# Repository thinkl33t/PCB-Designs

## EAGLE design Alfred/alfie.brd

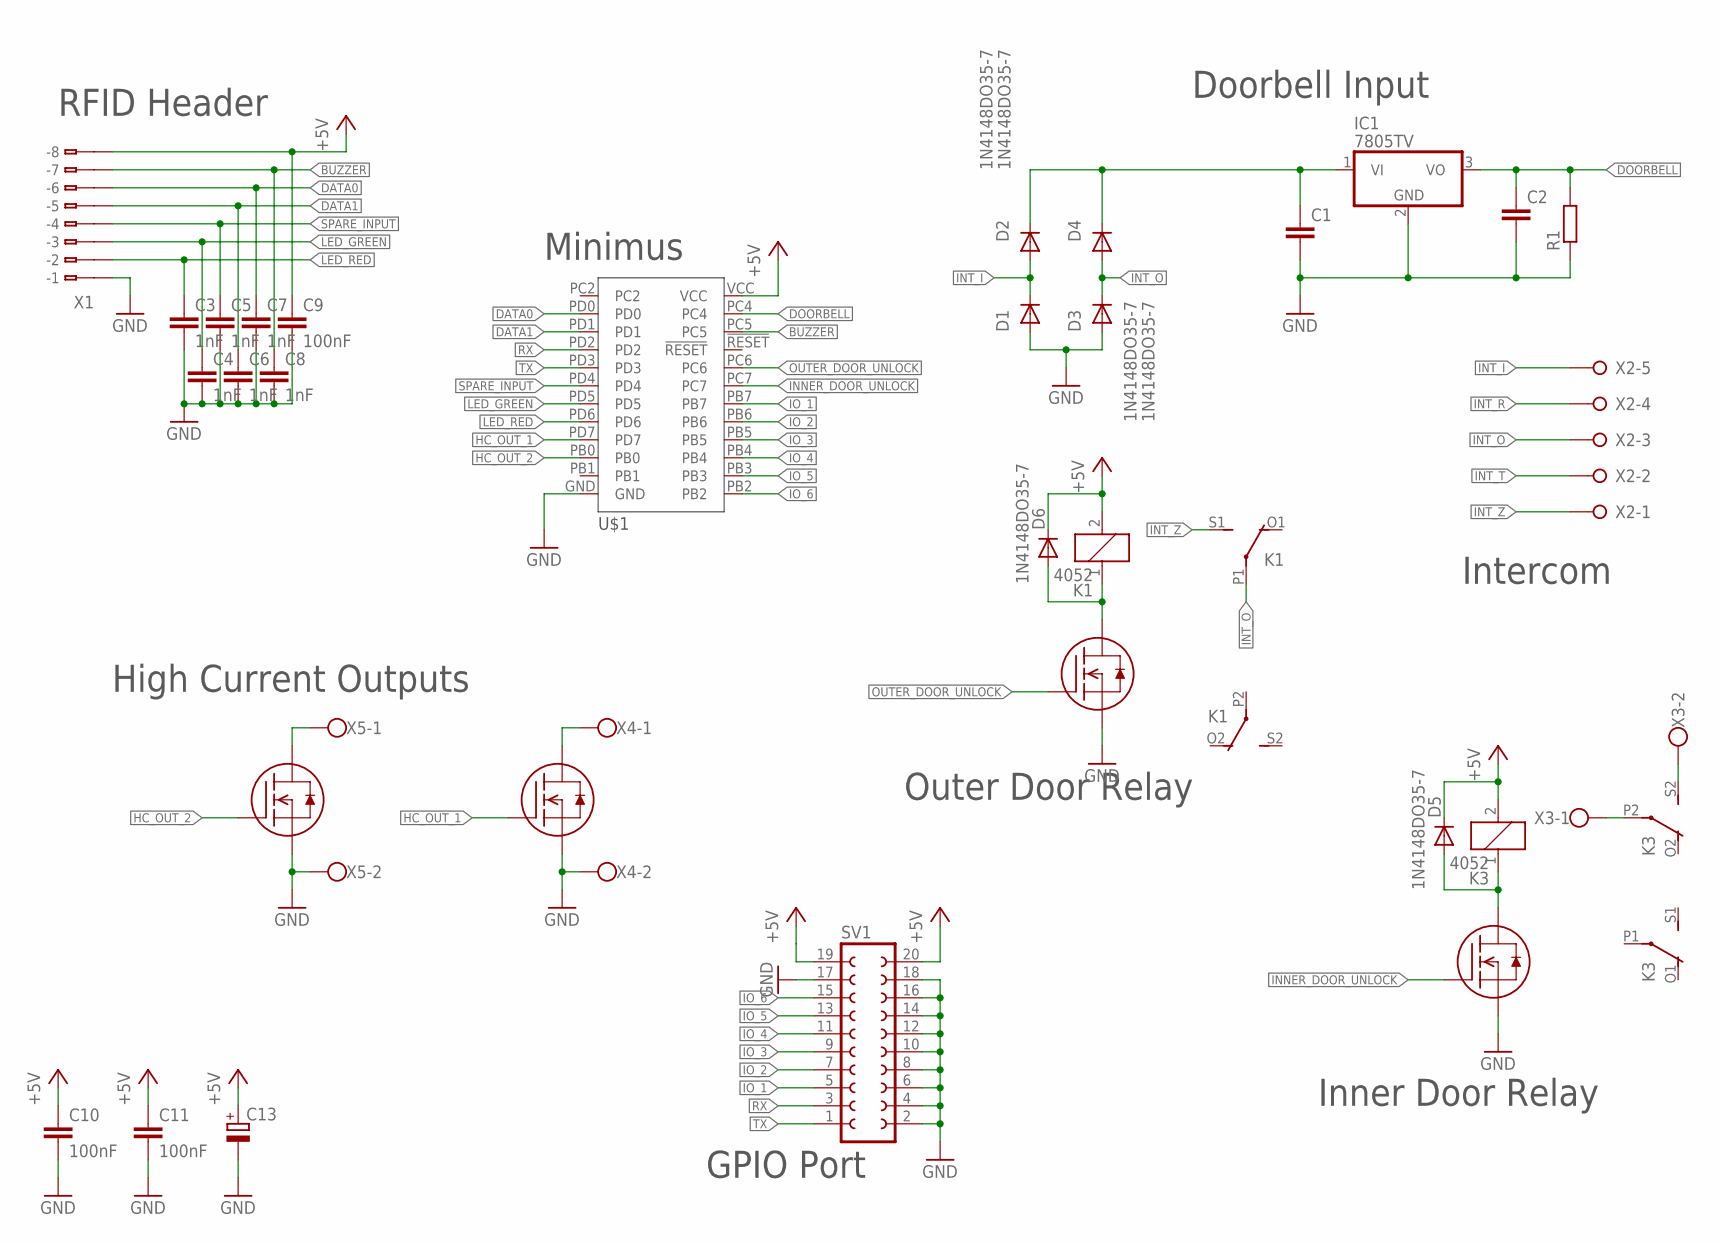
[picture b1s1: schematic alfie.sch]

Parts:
C1, C2: C-EU025-030X050; C025-030X050
C3, C4, C5, C6, C7, C8: 1nF; C0805
C9, C10, C11: 100nF; C0805
C13: CPOL-EUE5-8.5; E5-8,5
D1, D2, D3, D4, D5, D6: 1N4148DO35-7; DO35-7
IC1: 7805TV; TO220V
K1, K3: 4052; F4052
R1: R-EU_0207/10; 0207/10
SV1: FE10-2
U$1: MINIMUS
U$2, U$3, U$4, U$5: NTF3055L108T1GTAB; SOT223
X1: 233-508
X2: W237-05P; W237-5P
X3, X4, X5: W237-102

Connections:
+5V: C9.1, C10.1, C11.1, C13.+, D5.C, D6.C, K1.2, K3.2, SV1.19, SV1.20, U$1.VCC, X1.B8 (B-8)
BUZZER: C8.1, U$1.PC5, X1.B7 (B-7)
DATA0: C7.1, U$1.PD0, X1.B6 (B-6)
DATA1: C6.1, U$1.PD1, X1.B5 (B-5)
DOORBELL: C2.1, IC1.3 (VO), R1.2, U$1.PC4
GND: C1.2, C2.2, C3.2, C4.2, C5.2, C6.2, C7.2, C8.2, C9.2, C10.2, C11.2, C13.-, D1.A, D3.A, IC1.2 (GND), R1.1, SV1.2, SV1.4, SV1.6, SV1.8, SV1.10, SV1.12, SV1.14, SV1.16, SV1.17, SV1.18, U$1.GND, U$2.3 (S), U$3.3 (S), U$4.3 (S), U$5.3 (S), X1.B1 (B-1), X4.2, X5.2
HC_OUT_1: U$1.PD7, U$3.1 (G)
HC_OUT_2: U$1.PB0, U$4.1 (G)
INNER_DOOR_UNLOCK: U$1.PC7, U$5.1 (G)
INT_I: D1.C, D2.A, X2.5
INT_O: D3.C, D4.A, K1.P1, X2.3
INT_R: X2.4
INT_T: X2.2
INT_Z: K1.S1 (S), X2.1
IO_1: SV1.5, U$1.PB7
IO_2: SV1.7, U$1.PB6
IO_3: SV1.9, U$1.PB5
IO_4: SV1.11, U$1.PB4
IO_5: SV1.13, U$1.PB3
IO_6: SV1.15, U$1.PB2
LED_GREEN: C4.1, U$1.PD5, X1.B3 (B-3)
LED_RED: C3.1, U$1.PD6, X1.B2 (B-2)
unnamed: D6.A, K1.1, U$2.4 (D)
unnamed: D5.A, K3.1, U$5.4 (D)
unnamed: C1.1, D2.C, D4.C, IC1.1 (VI)
unnamed: K3.P2, X3.1
unnamed: U$3.4 (D), X4.1
unnamed: K3.S2 (S), X3.2
unnamed: U$4.4 (D), X5.1
OUTER_DOOR_UNLOCK: U$1.PC6, U$2.1 (G)
RX: SV1.3, U$1.PD2
SPARE_INPUT: C5.1, U$1.PD4, X1.B4 (B-4)
TX: SV1.1, U$1.PD3

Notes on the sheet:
Doorbell Input
Inner Door Relay
Outer Door Relay
Intercom
GPIO Port
High Current Outputs
Minimus
RFID Header

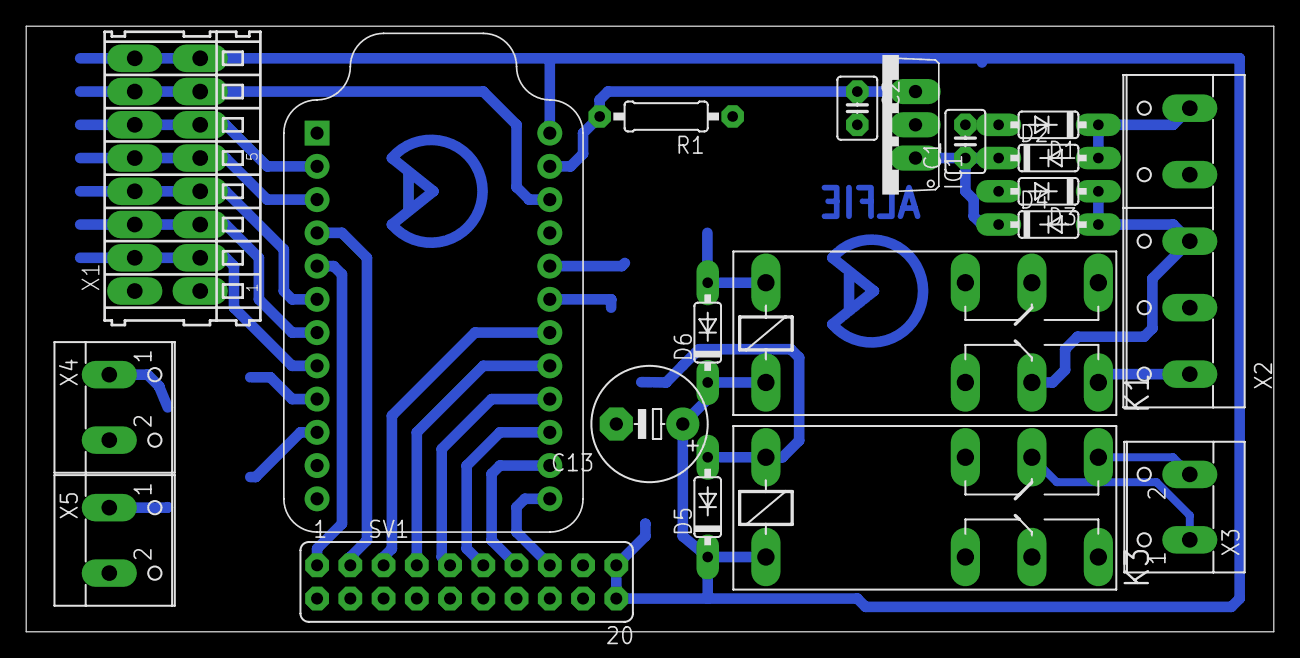
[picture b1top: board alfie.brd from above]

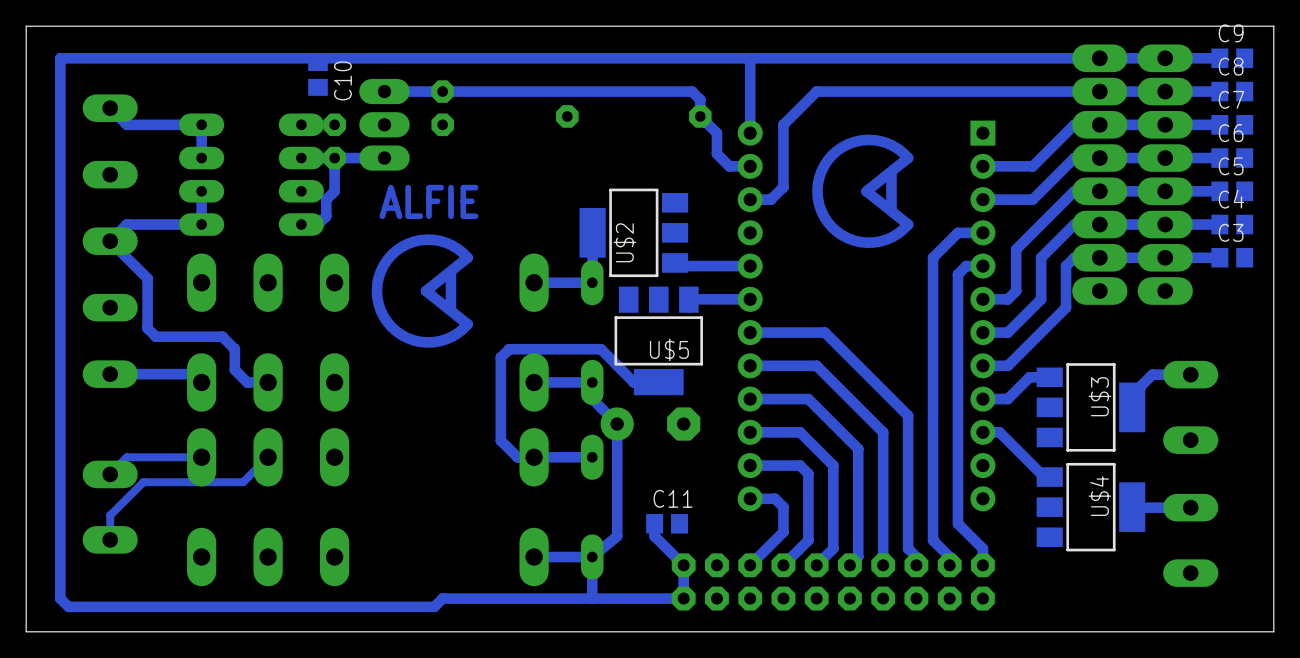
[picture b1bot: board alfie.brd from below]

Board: 2 copper layers, 95.3 x 46.3 mm, 33 parts (13 on the bottom side), 31 nets.
